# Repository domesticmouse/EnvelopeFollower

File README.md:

# ENV / SKEW Build Tutorial

An end-to-end, interactive human-in-the-loop engineering tutorial documenting the full 9-stage arc from **HAGIWO/ハギヲ** (`@solder_state`) Project **No. 43** — the hand-drawn **Hagiwo Sketch** ([`$4 Envelope Follower`](https://note.com/solder_state/n/n110e9ba066b3?hl=en), [`EnvelopeFollower.webp`](EnvelopeFollower.webp)) — through the **6 HP `ENV / SKEW`** Eurorack hardware (`2× TL074HIDR`, `30.0 × 108.0 mm` main PCB, `30.0 × 128.5 mm` Matte Black + ENIG Gold 3U front panel) using **Python (SKiDL)**, **KiCad 10**, and **VectorCraft**, and onward through `/wayfinder` planning to the live **Companion Site** launch.

> **Cross-Site Orientation:**
> - **Live Build Tutorial (this repository):** **[domesticmouse.github.io/EnvelopeFollower](https://domesticmouse.github.io/EnvelopeFollower/)** *(or read from [`site/src/content/tutorial/index.mdx`](site/src/content/tutorial/index.mdx) / serve locally with Astro Core on Node.js `24`)*
> - **Live `ENV / SKEW` Companion Site:** **[domesticmouse.github.io/EnvelopeFollowerWithSkewLimiter](https://domesticmouse.github.io/EnvelopeFollowerWithSkewLimiter/)** *(interactive **Patch Guides**, `211`-step **Build Checklists**, hardware showcase, and **Reference Specs**)*
> - **Hardware Source Repository:** [`domesticmouse/EnvelopeFollowerWithSkewLimiter`](https://github.com/domesticmouse/EnvelopeFollowerWithSkewLimiter) (pinned in `reference/` at [`164f50f`](https://github.com/domesticmouse/EnvelopeFollowerWithSkewLimiter/tree/164f50f))

<table align="center">
  <tr>
    <th>Matte Black + ENIG Front Panel</th>
    <th>Main PCB Front (<code>F.Cu</code> Controls)</th>
    <th>Main PCB Rear (<code>B.Cu</code> 50-SMD PCBA)</th>
  </tr>
  <tr>
    <td align="center"></td>
    <td align="center"></td>
    <td align="center"></td>
  </tr>
</table>

---

## Companion Reference Hardware & Companion Site (`164f50f`)

Every netlist rule, KiCad script, verification gate, manufacturing pack, **Build Checklist**, **Patch Guide**, and **Companion Site** workflow in this tutorial traces directly to [`domesticmouse/EnvelopeFollowerWithSkewLimiter`](https://github.com/domesticmouse/EnvelopeFollowerWithSkewLimiter) (`reference/` @ [`164f50f`](https://github.com/domesticmouse/EnvelopeFollowerWithSkewLimiter/tree/164f50f)):

- **6 HP Dual-Mode Hardware (`ENV / SKEW`):** Combines AC-coupled **Envelope Follower Mode** (`IN`, `J1`) and normal-broken DC-coupled **Asymmetric Skew Limiter Mode** (`SLEW IN`, `J2`) around `2× TL074HIDR` (`80` netlist components, `83` PCB footprints across `48` active nets): `50` Bottom-Side Economic SMDs across `17` rows in [`jlcpcb_bom.csv`](https://github.com/domesticmouse/EnvelopeFollowerWithSkewLimiter/blob/164f50f/jlcpcb_bom.csv) (`3` Extended SKUs), `18` manual through-hole parts in [`bom/ibom.html`](https://domesticmouse.github.io/EnvelopeFollowerWithSkewLimiter/bom/ibom.html), and `12` DNP Keystone test points (`TP1`–`TP12`).
- **Mated 3U Front Panel & Fabrication Packs:** Generated via `--blank-front` (`generate_eurorack_panel.py`), styled in Dark Techno / Brutalist Matte Black + White `F.SilkS` + ENIG Gold `F.Mask` with `vectorcraft-cli` (`40 px/mm` clearance audit), fractured via `SHAPE_POLY_SET` into KiCad 10, and bundled with dual-board Gerbers and CPL in [`manufacturing/`](https://github.com/domesticmouse/EnvelopeFollowerWithSkewLimiter/tree/164f50f/manufacturing).
- **Post-`4a02c46` Hardware Deliverables (`164f50f`):** Adds `81` deterministic visual **Build Checklist** PNGs (`pcba_alignment`, `hand_assembly`, `board_bringup`) backing [`checklists/`](https://github.com/domesticmouse/EnvelopeFollowerWithSkewLimiter/tree/164f50f/checklists), a real-world parts substitution record ([`tayda-1000489380.md`](https://github.com/domesticmouse/EnvelopeFollowerWithSkewLimiter/blob/164f50f/manufacturing/orders/tayda-1000489380.md)), and `8` musical **Patch Guides** ([`patches/`](https://github.com/domesticmouse/EnvelopeFollowerWithSkewLimiter/tree/164f50f/patches)) completing the `20`-file single-source hardware corpus.
- **25-Route Astro Core Companion Site:** Planned with `mattpocock/skills` and `/wayfinder` (`GLOSSARY.md`, `ADR 0001`, throwaway UI prototypes) and published as the live [**`ENV / SKEW` Companion Site**](https://domesticmouse.github.io/EnvelopeFollowerWithSkewLimiter/), compiling the `20` unmodified root Markdown files into `25` routes with `97` allowlisted **Static Passthroughs**, Pagefind search, Native Web Components, and `211`-step `localStorage` checklists.

> **Dual-Tier Submodule Pin ([`ADR 0002`](docs/adr/0002-copy-aligned-site-parity-and-dual-tier-submodule-pin.md)):** `reference/` and this **Living Context Map** track the live aligned **Companion Site** HEAD ([`164f50f`](https://github.com/domesticmouse/EnvelopeFollowerWithSkewLimiter/tree/164f50f)). All `13` tutorial MDX pages under `site/src/content/tutorial/`, [`PotentialImprovements.md`](PotentialImprovements.md), and [`docs/research/reference-github-trail.md`](docs/research/reference-github-trail.md) remain anchored to [`8ad81d0`](https://github.com/domesticmouse/EnvelopeFollowerWithSkewLimiter/tree/8ad81d0) as the immutable **Decision Trail** snapshot ([`PR #32`](https://github.com/domesticmouse/EnvelopeFollowerWithSkewLimiter/pull/32)).

---

## Tutorial Map

| Group | Section | Focus | File |
| :--- | :--- | :--- | :--- |
| **Overview** | **Overview** | 9-stage pipeline (`S0`–`S9`), prerequisites, panel I/O summary & cross-site orientation | [`site/src/content/tutorial/index.mdx`](site/src/content/tutorial/index.mdx) |
| **Hardware Build** | **Stage 1** | Hardware agent skills (`9` core + `vectorcraft-cli`), **Living Context Map**, `/agy-customizations` & skill smoke tests | [`site/src/content/tutorial/stages/01-hardware-agent-skills.mdx`](site/src/content/tutorial/stages/01-hardware-agent-skills.mdx) |
| **Hardware Build** | **Stage 2** | **Hagiwo Sketch** attribution, multi-scale extraction, KCL checks, Bode/Nyquist sweeps & doc linting | [`site/src/content/tutorial/stages/02-sketch-extraction-and-critique.mdx`](site/src/content/tutorial/stages/02-sketch-extraction-and-critique.mdx) |
| **Hardware Build** | **Stage 3** | Interactive Q&A → `DesignSpec.md`, `TP1`–`TP12` test strategy & BOM↔netlist checks | [`site/src/content/tutorial/stages/03-design-spec-and-dft.mdx`](site/src/content/tutorial/stages/03-design-spec-and-dft.mdx) |
| **Hardware Build** | **Stage 4** | SKiDL `80`-part capture, Dailywell `2MS1` footprint, 3-Extended-SKU budget & 9-section A3 schematic/PDF | [`site/src/content/tutorial/stages/04-skidl-and-schematic.mdx`](site/src/content/tutorial/stages/04-skidl-and-schematic.mdx) |
| **Hardware Build** | **Stage 5** | `6 HP` main PCB (`83` footprints), `silk_layout.json` & `/edit-silkscreen` hybrid GUI/AI loop | [`site/src/content/tutorial/stages/05-main-pcb-and-silkscreen.mdx`](site/src/content/tutorial/stages/05-main-pcb-and-silkscreen.mdx) |
| **Hardware Build** | **Stage 6** | Blank-front `5.2 mm` switch spec, `vectorcraft-cli` art & `SHAPE_POLY_SET` import | [`site/src/content/tutorial/stages/06-front-panel-and-artwork.mdx`](site/src/content/tutorial/stages/06-front-panel-and-artwork.mdx) |
| **Hardware Build** | **Stage 7** | Dual-board `manufacturing/` Gerbers, `81` visual **Build Checklist** renders, THT `ibom.html`, Tayda order record, `8` **Patch Guides** & `ruff` hygiene | [`site/src/content/tutorial/stages/07-fabrication-checklists-and-patches.mdx`](site/src/content/tutorial/stages/07-fabrication-checklists-and-patches.mdx) |
| **Companion Site** | **Stage 8** | `mattpocock/skills`, `/wayfinder` map, parallel research, HITL grilling (`GLOSSARY.md` + `ADR 0001`), prototypes & Spec `#17` | [`site/src/content/tutorial/stages/08-wayfinder-site-planning.mdx`](site/src/content/tutorial/stages/08-wayfinder-site-planning.mdx) |
| **Companion Site** | **Stage 9** | `/to-tickets` + `/implement-spec`, `25`-route Astro Core, 2-seam CI, `/code-review`, Chrome DevTools QA, Pages OIDC & **Repository Front Door** shift | [`site/src/content/tutorial/stages/09-companion-site-delivery.mdx`](site/src/content/tutorial/stages/09-companion-site-delivery.mdx) |
| **Optional Exploration** | **Optional: AC/DC Mode** | Adding `SW3` (`AC / DC`) across `C7` for `2×` LFO full-wave rectification | [`site/src/content/tutorial/optional/ac-dc-input-coupling.mdx`](site/src/content/tutorial/optional/ac-dc-input-coupling.mdx) |
| **Tutorial Appendix** | **Netlist, BOM & Silkscreen Schedule** | Canonical `80`-part design BOM, `17`-row `jlcpcb_bom.csv`, `48` nets & `silk_layout.json` | [`site/src/content/tutorial/appendix/netlist-and-bom.mdx`](site/src/content/tutorial/appendix/netlist-and-bom.mdx) |
| **Tutorial Appendix** | **Engineering Sign-Off Checklist** | 5-phase engineering, fabrication & **Companion Site** sign-off checklist (`8ad81d0`) | [`site/src/content/tutorial/appendix/engineering-sign-off-checklist.mdx`](site/src/content/tutorial/appendix/engineering-sign-off-checklist.mdx) |

---

## Repository Structure

```text
EnvelopeFollower/
├── AGENTS.md                              # Agent workflow rules & repo pointers
├── GLOSSARY.md                            # Canonical cross-repo domain vocabulary
├── site/                                  # Isolated Astro Core workspace (Node.js >= 24)
│   ├── astro.config.mjs                   # MDX, KaTeX, Shiki & remark/rehype pipeline
│   ├── package.json                       # Astro Core, Pagefind, Mermaid, @fontsource/*, Vitest
│   ├── scripts/check-site.ts              # Built-site & repo contract verifier CLI (`npm run check`)
│   ├── src/
│   │   ├── assets/images/                 # 14 unique images (8 renders + 3 checklists + 3 site WebPs)
│   │   ├── components/                    # PromptBlock, PromptGroup, Callout, Disclosure, Figure, Chrome
│   │   ├── content/tutorial/              # 13 MDX pages (Overview, Stages 1–9, Optional, Appendix)
│   │   ├── layouts/TutorialLayout.astro   # Unified 3-column Patchbay Workbench shell
│   │   ├── lib/                           # routes, panel-svg, site-contract, search/lightbox/copy
│   │   ├── plugins/                       # remark double-dollar math, mermaid, prompt-chips, code-console
│   │   └── styles/                        # Self-hosted @fontsource/* imports, tokens & workbench CSS
│   └── tests/                             # Vitest + happy-dom unit & contract suites
├── docs/                                  # Internal repo governance & engineering records (excluded from site)
│   ├── adr/                               # Architecture Decision Records (0001 MDX site, 0002 parity & dual-tier pin)
│   ├── agents/                            # Agent workflow contracts (issue tracker, triage labels, domain)
│   └── research/                          # Primary-source research notes
├── prompts/                               # 16 pre-Wayfinder hardware Session Traces (01–16) + README.md
├── reference/                             # Git submodule -> domesticmouse/EnvelopeFollowerWithSkewLimiter (164f50f)
├── .agents/skills/                        # Agent skills (agy-brain-explorer + mattpocock/skills suite)
├── .github/workflows/docs.yml             # Node.js 24 build, verifier & GitHub Pages deploy
├── EnvelopeFollower.webp                  # Original Hagiwo Sketch reference image
├── EVENT_ANNOUNCEMENT.md                  # Reusable announcement copy for live coding events
├── PotentialImprovements.md               # Standalone note on DC-coupled FWR bypass
├── skills-lock.json                       # Pinned upstream skill versions
└── LICENSE                                # Apache License 2.0
```

---

## Building & Verifying Docs Locally

Requires [Node.js `24` LTS](https://nodejs.org/) (`node >= 24.0.0`, `npm`) with zero Python or headless Chromium dependencies:

```bash
# Clone with companion hardware reference submodule
git clone --recurse-submodules https://github.com/domesticmouse/EnvelopeFollower.git
cd EnvelopeFollower/site

# Install dependencies and start live-reload Astro dev server
npm ci
npm run dev

# Full typecheck, Vitest suite, production build + Pagefind, and contract verification
npm run typecheck && npm test && npm run build && npm run check -- --require-reference
```

---

## Evidence Trails & Standalone Notes

- **Session Traces ([`prompts/README.md`](prompts/README.md)):** Stages 1–7 cite the `16` pre-Wayfinder exported transcripts (`01`–`16`), captured via [`.agents/skills/agy-brain-explorer/SKILL.md`](.agents/skills/agy-brain-explorer/SKILL.md).
- **Decision Trail (Public GitHub Record):** Stages 8–9 and this tutorial adaptation follow the public GitHub record:
  - Hardware planning map: [ENV / SKEW GitHub Pages Site & README Overhaul (`#4`)](https://github.com/domesticmouse/EnvelopeFollowerWithSkewLimiter/issues/4)
  - Hardware implementation spec: [ENV / SKEW GitHub Pages Site & README Overhaul — Implementation Specification (`#17`)](https://github.com/domesticmouse/EnvelopeFollowerWithSkewLimiter/issues/17)
  - Single-source site architecture: [`ADR 0001` — Astro Core Single-Source Site](https://github.com/domesticmouse/EnvelopeFollowerWithSkewLimiter/blob/164f50f/docs/adr/0001-astro-core-single-source-site.md)
  - Tutorial site architecture: [`ADR 0001` — Astro Core in `site/` with Relocated MDX Content Collections](docs/adr/0001-astro-core-mdx-tutorial-site.md)
  - Copy-aligned site parity & submodule pin policy: [`ADR 0002` — Copy-Aligned Site Parity and Dual-Tier Submodule Pin](docs/adr/0002-copy-aligned-site-parity-and-dual-tier-submodule-pin.md)
  - Tutorial adaptation map: [Adapt EnvelopeFollower Tutorial Docs to Updated ENV / SKEW Reference Repo (`#4`)](https://github.com/domesticmouse/EnvelopeFollower/issues/4)
  - Immutable historical snapshot: All `13` tutorial MDX pages, [`PotentialImprovements.md`](PotentialImprovements.md), and [`docs/research/reference-github-trail.md`](docs/research/reference-github-trail.md) remain anchored to [`8ad81d0`](https://github.com/domesticmouse/EnvelopeFollowerWithSkewLimiter/tree/8ad81d0) ([`PR #32`](https://github.com/domesticmouse/EnvelopeFollowerWithSkewLimiter/pull/32)).
- **Standalone Notes:** See [`PotentialImprovements.md`](PotentialImprovements.md) for the original Hagiwo-RefDes `SW1`-across-`C1` analysis and [`site/src/content/tutorial/optional/ac-dc-input-coupling.mdx`](site/src/content/tutorial/optional/ac-dc-input-coupling.mdx) ([live page](https://domesticmouse.github.io/EnvelopeFollower/optional/ac-dc-input-coupling/)) for its `ENV / SKEW` translation (`SW3` across `C7`).

---

## Running a Live Event

Hosting a workshop or live coding event based on this **Build Tutorial**? See [`EVENT_ANNOUNCEMENT.md`](EVENT_ANNOUNCEMENT.md) for reusable announcement copy linking to both the live **Build Tutorial** and the **Companion Site**.

---

## Attribution & License

- **Hardware Origin:** Built on **HAGIWO/ハギヲ** (`@solder_state`)’s open-source DIY [No. 43: $4 Envelope Follower](https://note.com/solder_state/n/n110e9ba066b3?hl=en) (`2022-01-28`, [YouTube build demo](https://www.youtube.com/watch?v=0eHllqHmlZQ), [`EnvelopeFollower.webp`](EnvelopeFollower.webp)).
- **License:** Licensed under the [Apache License 2.0](LICENSE).

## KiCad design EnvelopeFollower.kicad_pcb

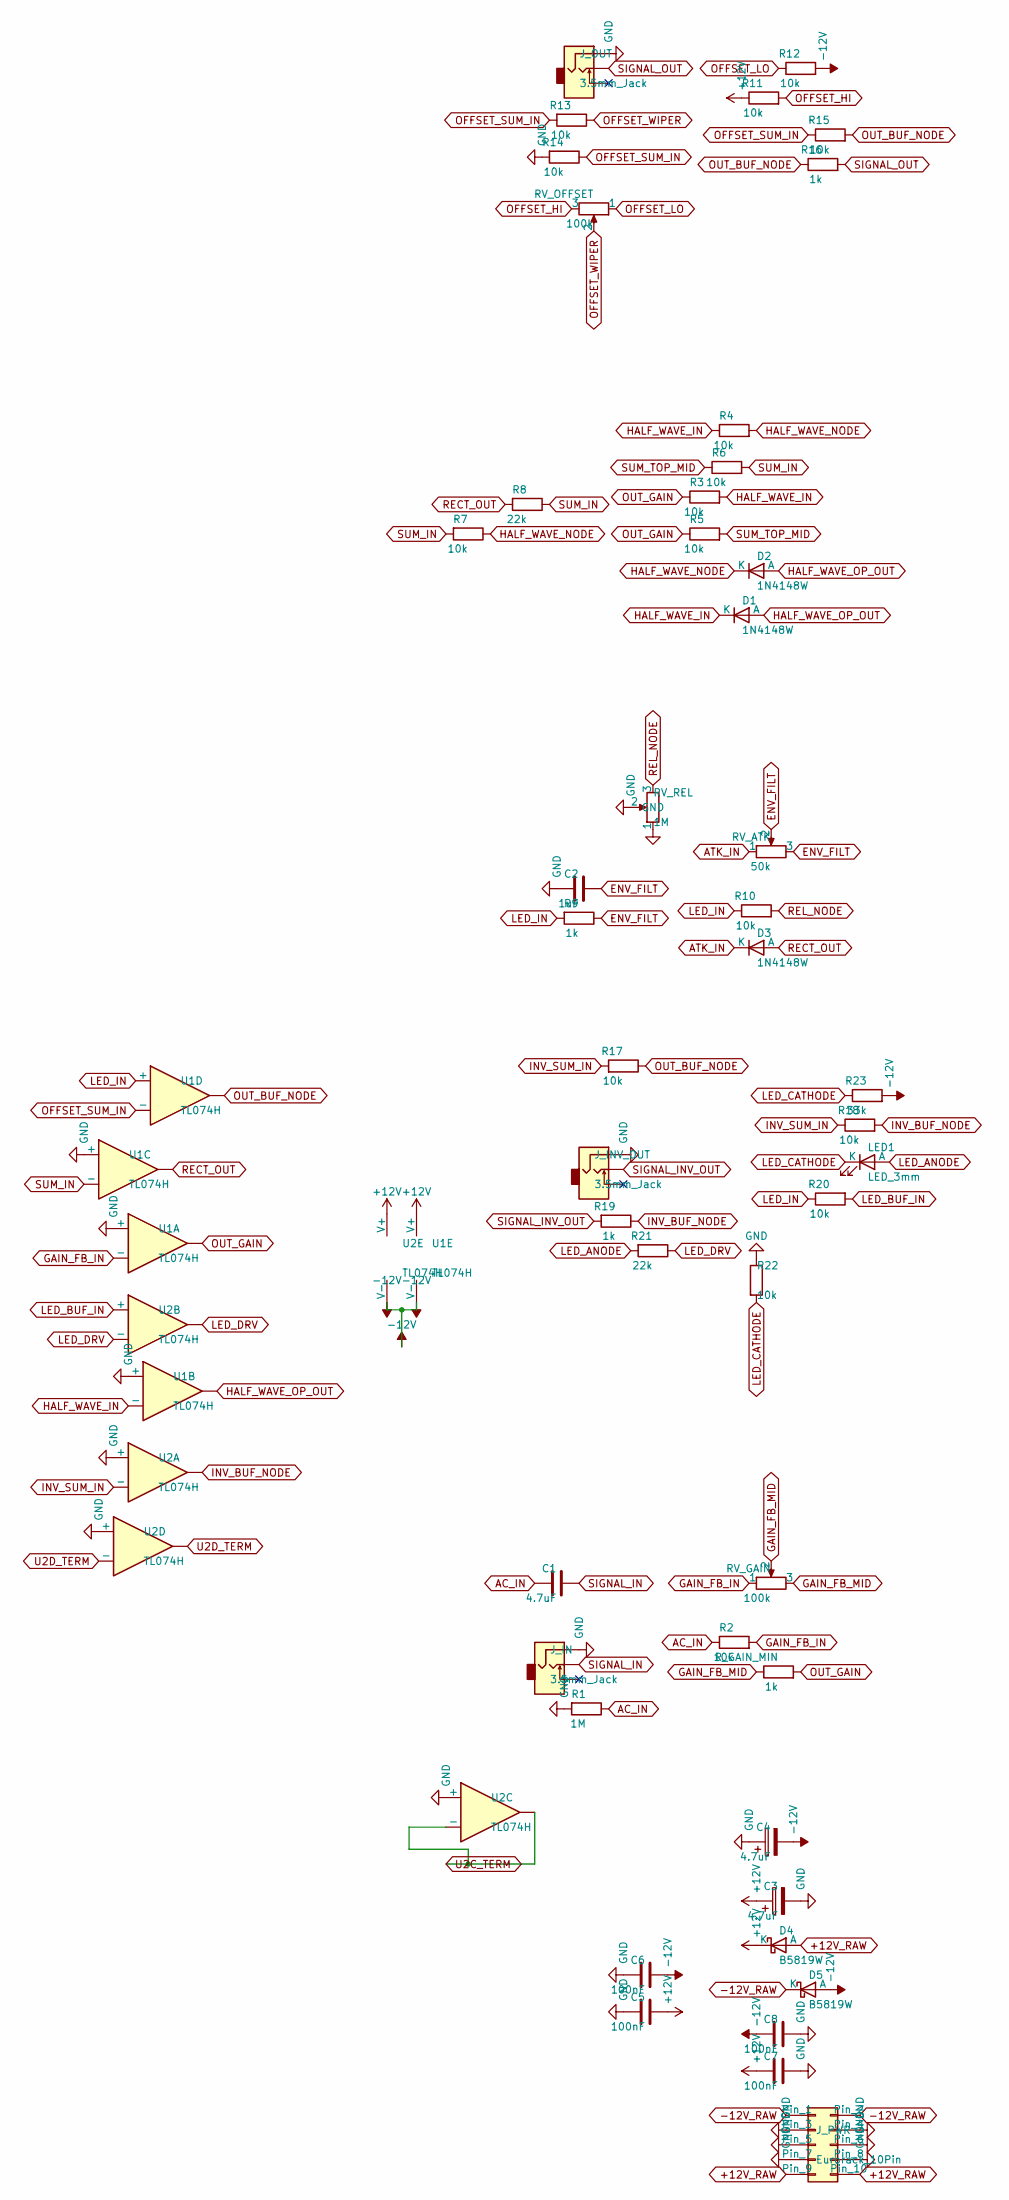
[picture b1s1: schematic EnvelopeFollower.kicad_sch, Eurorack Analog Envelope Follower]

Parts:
C1: 4.7uF; C_0805_2012Metric; MPN CC0805KKX7R8BB475; LCSC C354262
C2: 1uF; C_0603_1608Metric; MPN CC0603KRX7R9BB105; LCSC C559769
C3, C4: 4.7uF; CP_Elec_4x5.4; MPN VT4.7UF50V167RV0133; LCSC C5246584
C5, C6, C7, C8: 100nF; C_0603_1608Metric; MPN CC0603KRX7R9BB104; LCSC C14663
D1, D2, D3: 1N4148W; D_SOD-123; MPN 1N4148W; LCSC C81598
D4, D5: B5819W; D_SOD-123; MPN B5819W SL; LCSC C8598
J_IN: 3.5mm_Jack; Jack_3.5mm_QingPu_WQP-PJ398SM_Vertical_CircularHoles; JLCPCB_Class Manual THT
J_INV_OUT: 3.5mm_Jack; Jack_3.5mm_QingPu_WQP-PJ398SM_Vertical_CircularHoles; JLCPCB_Class Manual THT
J_OUT: 3.5mm_Jack; Jack_3.5mm_QingPu_WQP-PJ398SM_Vertical_CircularHoles; JLCPCB_Class Manual THT
J_PWR: Eurorack_10Pin; IDC-Header_2x05_P2.54mm_Vertical; MPN IDC2.54-2*5PZ; LCSC C53207560
LED1: LED_3mm; LED_D3.0mm; JLCPCB_Class Manual THT
R1: 1M; R_0603_1608Metric; MPN 0603WAF1004T5E; LCSC C22935
R2, R3, R4, R5, R6, R7, R10, R11, R12, R13, R14, R15, R17, R18, R20, R22: 10k; R_0603_1608Metric; MPN 0603WAF1002T5E; LCSC C25804
R8, R21: 22k; R_0603_1608Metric; MPN 0603WAF2202T5E; LCSC C31850
R9, R16, R19: 1k; R_0603_1608Metric; MPN 0603WAF1001T5E; LCSC C21190
R23: 33k; R_0603_1608Metric; MPN 0603WAF3302T5E; LCSC C4216
RV_ATK: 50k; Potentiometer_Alpha_RD901F-40-00D_Single_Vertical; JLCPCB_Class Manual THT
RV_GAIN: 100k; Potentiometer_Alpha_RD901F-40-00D_Single_Vertical; JLCPCB_Class Manual THT
RV_OFFSET: 100k; Potentiometer_Alpha_RD901F-40-00D_Single_Vertical; JLCPCB_Class Manual THT
RV_REL: 1M; Potentiometer_Alpha_RD901F-40-00D_Single_Vertical; JLCPCB_Class Manual THT
R_GAIN_MIN: 1k; R_0603_1608Metric; MPN 0603WAF1001T5E; LCSC C21190
U1, U2: TL074H; SOIC-14_3.9x8.7mm_P1.27mm; MPN TL074HIDR; LCSC C2878713

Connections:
+12V: C3.1, C5.1, C7.1, D4.1 (K), R11.1, U1.4 (V+), U2.4 (V+)
+12V_RAW: D4.2 (A), J_PWR.9, J_PWR.10
-12V: C4.2, C6.1, C8.1, D5.2 (A), R12.2, R23.2, U1.11 (V-), U2.11 (V-)
-12V_RAW: D5.1 (K), J_PWR.1, J_PWR.2
AC_IN: C1.2, R1.1, R2.1
ATK_IN: D3.1 (K), RV_ATK.1
ENV_FILT: C2.1, R9.1, RV_ATK.2, RV_ATK.3
GAIN_FB_IN: R2.2, RV_GAIN.1, U1.2 (-)
GAIN_FB_MID: RV_GAIN.2, RV_GAIN.3, R_GAIN_MIN.1
GND: C2.2, C3.2, C4.1, C5.2, C6.2, C7.2, C8.2, J_IN.S, J_INV_OUT.S, J_OUT.S, J_PWR.3, J_PWR.4, J_PWR.5, J_PWR.6, J_PWR.7, J_PWR.8, R1.2, R14.2, R22.1, RV_REL.1, RV_REL.2, U1.3 (+), U1.5 (+), U1.10 (+), U2.3 (+), U2.10 (+), U2.12 (+)
HALF_WAVE_IN: D1.1 (K), R3.2, R4.1, U1.6 (-)
HALF_WAVE_NODE: D2.1 (K), R4.2, R7.1
HALF_WAVE_OP_OUT: D1.2 (A), D2.2 (A), U1.7
INV_BUF_NODE: R18.2, R19.1, U2.1
INV_SUM_IN: R17.2, R18.1, U2.2 (-)
LED_ANODE: LED1.2 (A), R21.2
LED_BUF_IN: R20.2, U2.5 (+)
LED_CATHODE: LED1.1 (K), R22.2, R23.1
LED_DRV: R21.1, U2.6 (-), U2.7
LED_IN: R9.2, R10.1, R20.1, U1.12 (+)
OFFSET_HI: R11.2, RV_OFFSET.3
OFFSET_LO: R12.1, RV_OFFSET.1
OFFSET_SUM_IN: R13.2, R14.1, R15.1, U1.13 (-)
OFFSET_WIPER: R13.1, RV_OFFSET.2
OUT_BUF_NODE: R15.2, R16.1, R17.1, U1.14
OUT_GAIN: R3.1, R5.1, R_GAIN_MIN.2, U1.1
RECT_OUT: D3.2 (A), R8.2, U1.8
REL_NODE: R10.2, RV_REL.3
SIGNAL_IN: C1.1, J_IN.T
SIGNAL_INV_OUT: J_INV_OUT.T, R19.2
SIGNAL_OUT: J_OUT.T, R16.2
SUM_IN: R6.2, R7.2, R8.1, U1.9 (-)
SUM_TOP_MID: R5.2, R6.1
U2C_TERM: U2.8, U2.9 (-)
U2D_TERM: U2.13 (-), U2.14

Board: 2 copper layers, 48 parts (40 on the bottom side), 35 nets, no tracks yet.

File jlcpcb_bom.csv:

Comment,Designator,Footprint,LCSC Part #
TL074H,"U1, U2",SOIC-14_3.9x8.7mm_P1.27mm,C2878713
B5819W,"D4, D5",D_SOD-123,C8598
4.7uF,"C3, C4",CP_Elec_4x5.4,C5246584
100nF,"C5, C6, C7, C8",C_0603_1608Metric,C14663
4.7uF,C1,C_0805_2012Metric,C354262
1M,R1,R_0603_1608Metric,C22935
10k,"R2, R3, R4, R5, R6, R7, R10, R11, R12, R13, R14, R15, R17, R18, R20, R22",R_0603_1608Metric,C25804
1k,"R_GAIN_MIN, R9, R16, R19",R_0603_1608Metric,C21190
22k,"R8, R21",R_0603_1608Metric,C31850
1N4148W,"D1, D2, D3",D_SOD-123,C81598
1uF,C2,C_0603_1608Metric,C559769
33k,R23,R_0603_1608Metric,C4216

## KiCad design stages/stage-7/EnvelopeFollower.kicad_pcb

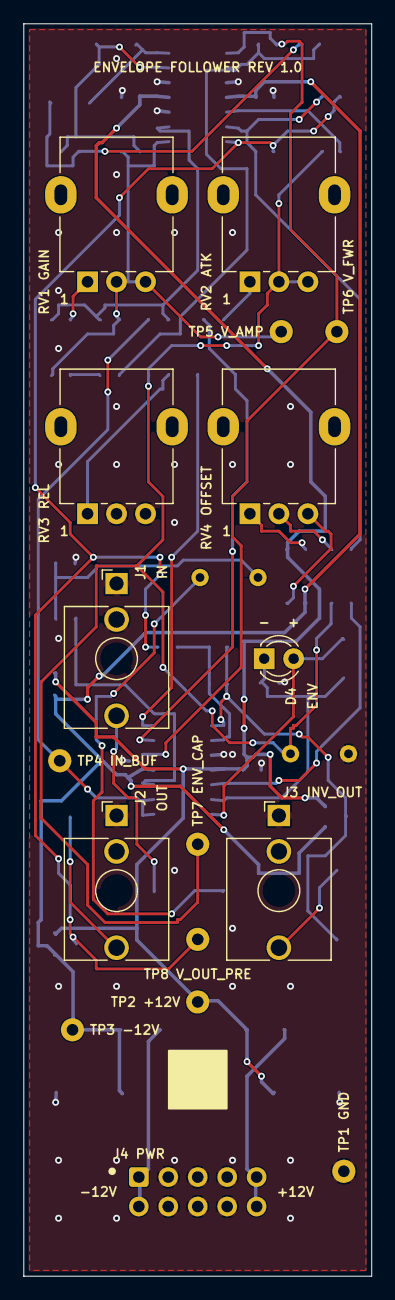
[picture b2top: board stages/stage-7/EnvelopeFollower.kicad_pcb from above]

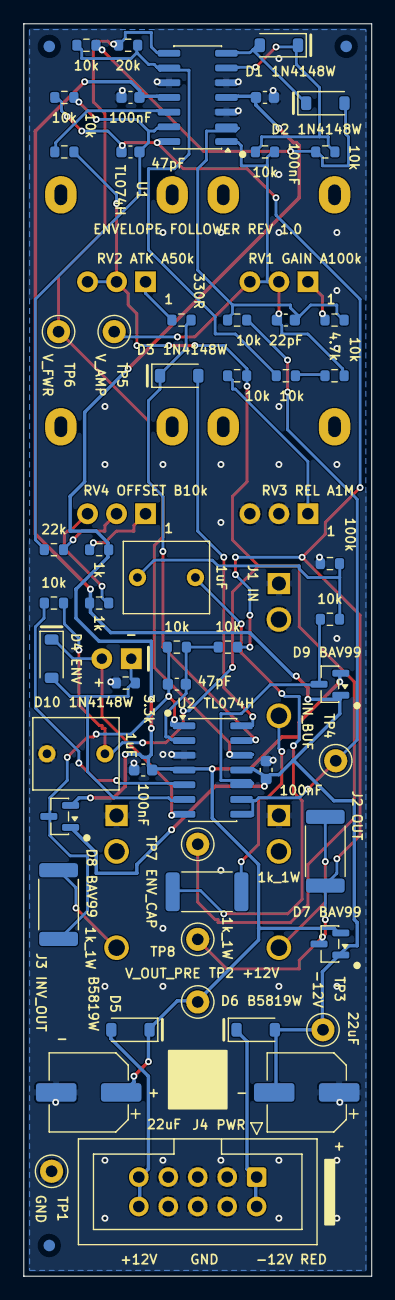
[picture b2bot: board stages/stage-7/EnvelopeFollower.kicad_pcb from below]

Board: 2 copper layers, 30.0 x 108.0 mm, 66 parts (58 on the bottom side), 37 nets.

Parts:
C1, C2: 1uF 63V; C_Rect_L7.2mm_W6.0mm_P5.00mm
C3, C4: 22uF 50V; CP_Elec_6.3x5.4
C5, C6, C7, C8: 100nF; C_0603_1608Metric
C9: 22pF; C_0603_1608Metric
C10, C11: 47pF; C_0603_1608Metric
D1, D2, D3, D10: 1N4148W; D_SOD-123
D4: LED_3mm_YG; LED_D3.0mm
D5, D6: B5819W; D_SOD-123
D7, D8, D9: BAV99; SOT-23
FID1, FID2, FID3: Fiducial; Fiducial_1mm_Mask2mm
J1: IN; Jack_3.5mm_QingPu_WQP-PJ398SM_Vertical_CircularHoles
J2: OUT; Jack_3.5mm_QingPu_WQP-PJ398SM_Vertical_CircularHoles
J3: INV_OUT; Jack_3.5mm_QingPu_WQP-PJ398SM_Vertical_CircularHoles
J4: Eurorack_Power_2x5; IDC-Header_2x05_P2.54mm_Vertical
R1: 100k; R_0603_1608Metric
R2, R3, R4, R5, R6, R7, R9, R10, R15, R17, R18, R20, R27: 10k; R_0603_1608Metric
R8: 20k; R_0603_1608Metric
R11, R12: 1k; R_0603_1608Metric
R13: 22k; R_0603_1608Metric
R16, R19, R26: 1k 1W; R_2512_6332Metric
R21: 3.3k; R_0603_1608Metric
R24: 4.7k; R_0603_1608Metric
R25: 330R; R_0603_1608Metric
RV1: A100k; Potentiometer_Alpha_RD901F-40-00D_Single_Vertical
RV2: A50k; Potentiometer_Alpha_RD901F-40-00D_Single_Vertical
RV3: A1M; Potentiometer_Alpha_RD901F-40-00D_Single_Vertical
RV4: B10k; Potentiometer_Alpha_RD901F-40-00D_Single_Vertical
TP1: GND; TestPoint_Keystone_5000-5004_Miniature
TP2: +12V; TestPoint_Keystone_5000-5004_Miniature
TP3: -12V; TestPoint_Keystone_5000-5004_Miniature
TP4: IN_BUF; TestPoint_Keystone_5000-5004_Miniature
TP5: V_AMP; TestPoint_Keystone_5000-5004_Miniature
TP6: V_FWR; TestPoint_Keystone_5000-5004_Miniature
TP7: ENV_CAP; TestPoint_Keystone_5000-5004_Miniature
TP8: V_OUT_PRE; TestPoint_Keystone_5000-5004_Miniature
U1, U2: TL074HIDR; SOIC-14_3.9x8.7mm_P1.27mm

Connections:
+12V: C3.1, C5.1, C7.1, D5.1, D7.2, D8.2, D9.2, R11.1, TP2.1, U1.4, U2.4
+12V_IN: D5.2, J4.9, J4.10
-12V: C4.2, C6.1, C8.1, D6.2, D7.1, D8.1, D9.1, R12.2, TP3.1, U1.11, U2.11
-12V_IN: D6.1, J4.1, J4.2
AC_IN: C1.2, R1.1, R27.1
ATK_IN: D3.1, R25.1, U2.13
ATK_POT_IN: R25.2, RV2.1
ENV_CAP: C2.1, R9.1, R10.1, R20.1, RV2.2, RV2.3, TP7.1
FF_MID: R6.2, R7.1
GAIN_MID: R24.2, RV1.1
GND: C2.2, C3.2, C4.1, C5.2, C6.2, C7.2, C8.2, J1.S, J1.TN, J2.S, J3.S, J4.3, J4.4, J4.5, J4.6, J4.7, J4.8, R1.2, R21.2, RV3.2, RV3.3, TP1.1, U1.3, U1.5, U1.10, U2.3
INV_OUT_TIP: J3.T, R19.2
IN_BUF: R2.1, TP4.1, U2.8, U2.9
IN_SURGE: C1.1, R26.2
IN_TIP: J1.T, R26.1
LED_A: D4.2, D10.1, U2.7
LED_K: D4.1, D10.2, R21.1, U2.6
OFFSET_BOT: R12.1, RV4.3
OFFSET_TOP: R11.2, RV4.1
OFFSET_WIPER: R13.1, RV4.2
OUT_TIP: J2.T, R16.2
REL_MID: R10.2, RV3.1
U1A_IN_M: C9.1, R2.2, R24.1, U1.2
U1B_IN_M: D1.1, R3.2, R4.1, U1.6
U1B_OUT: D1.2, D2.1, U1.7
U1C_IN_M: R5.2, R7.2, R8.1, U1.9
U1D_IN_M: C10.1, R13.2, R15.1, U1.13
U1D_IN_P: R9.2, U1.12
U2A_IN_M: C11.1, R17.2, R18.1, U2.2
U2B_IN_P: R20.2, U2.5
U2C_IN_P: D9.3, R27.2, U2.10
U2D_OUT: D3.2, U2.14
V_AMP: C9.2, R3.1, R6.1, RV1.2, RV1.3, TP5.1, U1.1
V_FWR: R8.2, TP6.1, U1.8, U2.12
V_INV_PRE: C11.2, D8.3, R18.2, R19.1, U2.1
V_OUT_PRE: C10.2, D7.3, R15.2, R16.1, R17.1, TP8.1, U1.14
V_RECT: D2.2, R4.2, R5.1

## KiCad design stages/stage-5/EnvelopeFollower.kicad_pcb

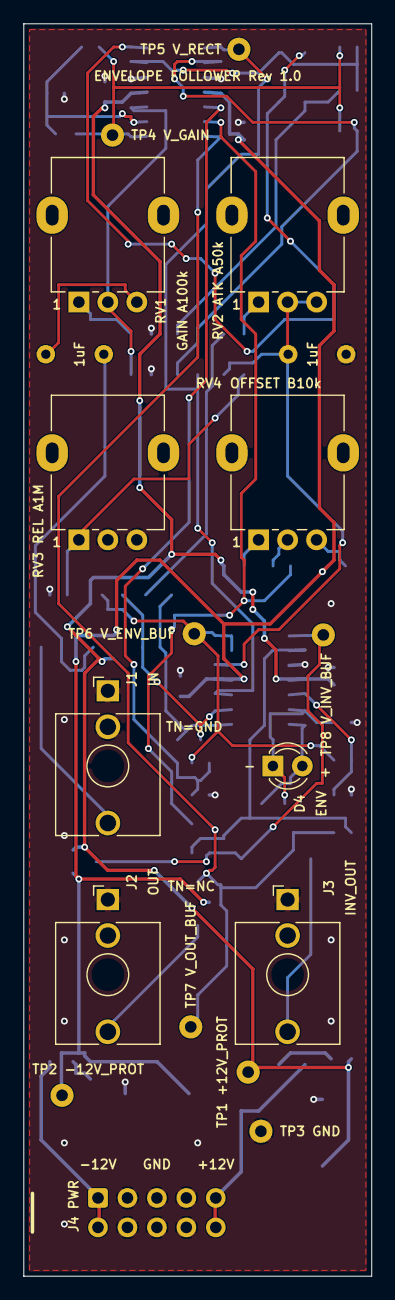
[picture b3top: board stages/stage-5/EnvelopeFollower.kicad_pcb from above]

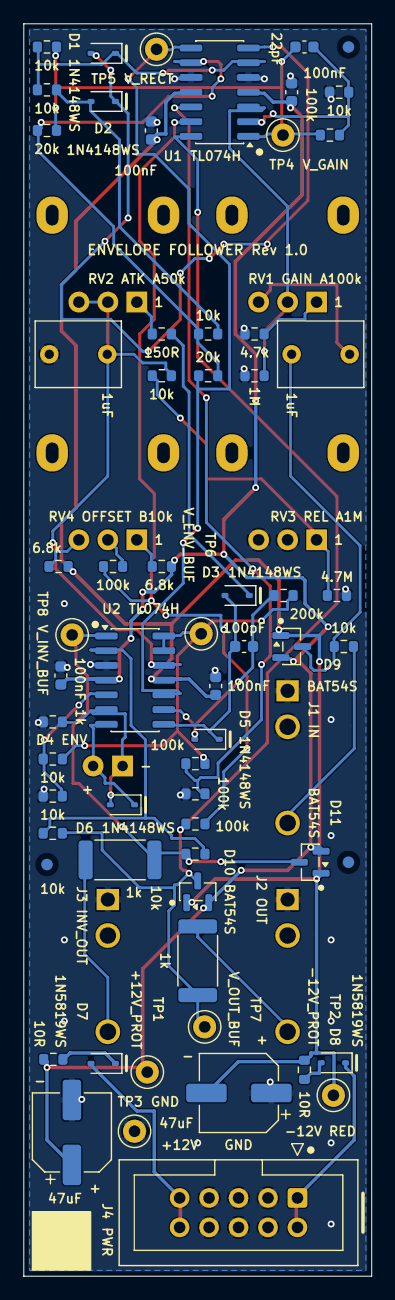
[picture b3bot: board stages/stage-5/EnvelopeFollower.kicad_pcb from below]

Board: 2 copper layers, 30.0 x 108.0 mm, 71 parts (63 on the bottom side), 39 nets.

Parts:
C1, C2: 1uF 63V; C_Rect_L7.2mm_W5.5mm_P5.00mm_FKS2_FKP2_MKS2_MKP2
C3, C4: 47uF 35V; CP_Elec_6.3x5.4
C5, C6, C7, C8: 100nF 50V; C_0603_1608Metric
C9: 22pF 50V; C_0603_1608Metric
C10: 100pF 50V; C_0603_1608Metric
D1, D2, D3, D5, D6: 1N4148WS; D_SOD-323
D4: 3mm Green LED; LED_D3.0mm
D7, D8: 1N5819WS; D_SOD-323
D9, D10, D11: BAT54S; SOT-23
FID1, FID2, FID3: Fiducial; Fiducial_1mm_Mask2mm
J1: IN; Jack_3.5mm_QingPu_WQP-PJ398SM_Vertical_CircularHoles
J2: OUT; Jack_3.5mm_QingPu_WQP-PJ398SM_Vertical_CircularHoles
J3: INV_OUT; Jack_3.5mm_QingPu_WQP-PJ398SM_Vertical_CircularHoles
J4: PWR_2x5; IDC-Header_2x05_P2.54mm_Vertical
R1, R4, R6, R7, R9, R13, R22, R23, R25, R26: 10k; R_0603_1608Metric
R2: 4.7k; R_0603_1608Metric
R3: 1M; R_0603_1608Metric
R5, R15, R16, R19, R20: 100k; R_0603_1608Metric
R8, R10: 20k; R_0603_1608Metric
R11: 200k; R_0603_1608Metric
R12: 150R; R_0603_1608Metric
R14: 4.7M; R_0603_1608Metric
R17, R18: 6.8k; R_0603_1608Metric
R21, R24: 1k 1W; R_2512_6332Metric
R27: 1k; R_0603_1608Metric
R28, R29: 10R; R_0603_1608Metric
RV1: A100k; Potentiometer_Alpha_RD901F-40-00D_Single_Vertical
RV2: A50k; Potentiometer_Alpha_RD901F-40-00D_Single_Vertical
RV3: A1M; Potentiometer_Alpha_RD901F-40-00D_Single_Vertical
RV4: B10k; Potentiometer_Alpha_RD901F-40-00D_Single_Vertical
TP1: +12V_PROT; TestPoint_Keystone_5000-5004_Miniature
TP2: -12V_PROT; TestPoint_Keystone_5000-5004_Miniature
TP3: GND; TestPoint_Keystone_5000-5004_Miniature
TP4: V_GAIN; TestPoint_Keystone_5000-5004_Miniature
TP5: V_RECT; TestPoint_Keystone_5000-5004_Miniature
TP6: V_ENV_BUF; TestPoint_Keystone_5000-5004_Miniature
TP7: V_OUT_BUF; TestPoint_Keystone_5000-5004_Miniature
TP8: V_INV_BUF; TestPoint_Keystone_5000-5004_Miniature
U1, U2: TL074H; SOIC-14_3.9x8.7mm_P1.27mm

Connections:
+12V_FILT_IN: D7.1, R28.1
+12V_IN: D7.2, J4.9, J4.10
+12V_PROT: C3.1, C5.1, C7.1, D9.2, D10.2, D11.2, R17.1, R28.2, TP1.1, U1.4, U2.4
-12V_FILT_IN: D8.2, R29.1
-12V_IN: D8.1, J4.1, J4.2
-12V_PROT: C4.2, C6.1, C8.1, D9.1, D10.1, D11.1, R18.1, R29.2, TP2.1, U1.11, U2.11
ATK_MID: R12.2, RV2.1
ENV_CAP: C2.1, R13.1, RV2.2, RV2.3, U2.12
GND: C2.2, C3.2, C4.1, C5.2, C6.2, C7.2, C8.2, J1.S, J1.TN, J2.S, J3.S, J4.3, J4.4, J4.5, J4.6, J4.7, J4.8, R2.2, R3.2, R4.2, R14.2, R16.2, R26.2, R27.2, RV3.2, RV3.3, TP3.1, U1.5, U1.10, U2.3
INV_OUT_TIP: J3.T, R24.2
INV_SUM: R22.2, R23.1, U2.2
IN_CLAMP: C1.1, D9.3, R1.2
IN_GAIN_INV: C9.1, R4.1, R5.1, U1.2
IN_POT_BOT: R2.1, RV1.1
IN_POT_TOP: C1.2, RV1.3
IN_TIP: J1.T, R1.1
IN_WIPER: R3.1, RV1.2, U1.3
LED_REF_IN: R25.2, R26.1, U2.5
LED_SENSE: D4.1, D6.2, R27.1, U2.6
OFF_BOT: R18.2, RV4.3
OFF_TOP: R17.2, RV4.1
OFF_WIPER: R19.1, RV4.2
OUT_INV_NODE: R19.2, R20.1, U1.13
OUT_NONINV: R15.2, R16.1, U1.12
OUT_TIP: J2.T, R21.2
PEAK_INV: C10.1, D5.2, R11.2, U2.9
PEAK_OP_OUT: C10.2, D3.2, D5.1, U2.8
RECT_DIODE_OUT: D3.1, R12.1
RECT_INV: D1.1, R6.2, R7.1, U1.6
RECT_MID: D2.2, R7.2, R9.1
RECT_OP_OUT: D1.2, D2.1, U1.7
REL_MID: R13.2, R14.1, RV3.1
SUM_INV: R8.2, R9.2, R10.1, U1.9
V_ENV_BUF: R11.1, R15.1, R25.1, TP6.1, U2.13, U2.14
V_GAIN: C9.2, R5.2, R6.1, R8.1, TP4.1, U1.1
V_INV_BUF: D11.3, R23.2, R24.1, TP8.1, U2.1
V_LED_DRV: D4.2, D6.1, U2.7
V_OUT_BUF: D10.3, R20.2, R21.1, R22.1, TP7.1, U1.14
V_RECT: R10.2, TP5.1, U1.8, U2.10

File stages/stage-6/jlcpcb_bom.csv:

Comment,Designator,Footprint,LCSC Part #
TL074H,"U1, U2",SOIC-14_3.9x8.7mm_P1.27mm,C2878713
100nF 50V,"C5, C6, C7, C8",C_0603_1608Metric,C14663
1N5819WS,"D7, D8",D_SOD-323,C191023
10R,"R28, R29",R_0603_1608Metric,C22859
47uF 35V,"C3, C4",CP_Elec_6.3x5.4,C2836440
10k,"R1, R4, R6, R7, R9, R13, R22, R23, R25, R26",R_0603_1608Metric,C25804
BAT54S,"D9, D10, D11",SOT-23,C47546
4.7k,R2,R_0603_1608Metric,C23162
1M,R3,R_0603_1608Metric,C22935
100k,"R5, R15, R16, R19, R20",R_0603_1608Metric,C25803
22pF 50V,C9,C_0603_1608Metric,C1653
20k,"R8, R10",R_0603_1608Metric,C4184
1N4148WS,"D1, D2, D3, D5, D6",D_SOD-323,C2128
200k,R11,R_0603_1608Metric,C25811
100pF 50V,C10,C_0603_1608Metric,C14858
150R,R12,R_0603_1608Metric,C22808
4.7M,R14,R_0603_1608Metric,C23163
6.8k,"R17, R18",R_0603_1608Metric,C23212
1k 1W,"R21, R24",R_2512_6332Metric,C54315
1k,R27,R_0603_1608Metric,C21190
